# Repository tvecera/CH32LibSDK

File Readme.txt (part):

=================================================================
FORK: Additional Features in This Fork
=================================================================

- Added support for **CH32V003-GameConsole** with the name **TinyBoy**,
  using the **CH32V002J4M6** MCU (_devices/tinyboy/README.md)
- Added support for **Olimex RVPC** _devices/rvpc/README.md)
- Added shell scripts for macOS and Linux for easier programming and building

CH32LibSDK - SDK library for low-end CH32 RISC-V microcontrollers
=================================================================
Pre-alpha version 0.39, under development.

Copyright (c) 2025 Miroslav Nemecek

Panda38@seznam.cz
hardyplotter2@gmail.com
https://github.com/Panda381/CH32LibSDK
https://www.breatharian.eu/hw/ch32libsdk/index_en.html

How to compile on Windows, using command line:

- Use FAR Manager to edit source files and run BAT scripts.
- Download MounRiver Studio v1.92 http://mounriver.com/download
- Install MounRiver Studio. 
- Extract "toolchain\RISC-V Embedded GCC12" compiler to separate folder.
- Edit _c1.bat file and enter path to "bin" folder of the compiler:
   set GCC_CH32_PATH=C:\GCC_CH32\bin
- Extract "toolchain\OpenOCD\bin" tool or use openocd from _tools\openocd.
- Sometimes you may need to use WCH-LinkUtility from the ExTool\SQWTool folder.
  It may sometimes be necessary to erase the flash memory using power-off,
  because OpenOcd cannot do this.
- Compile sample using c.bat.
- Flash compiled sample using e.bat with WCH-LinkE programmer (available here,
  for example: https://pajenicko.cz/usb-programator-a-debug-adapter-wch-link ).
  For the SD card version of the console, simply upload the program to the
  SD card and load it into the processor using the boot loader.
- Clear compilation using d.bat.

AntCalc
-------
AntCalc is a wrist-worn programmable calculator with scientific functions. It
features an inexpensive CH32V002A4M6 processor, a blue-yellow 0.96" I2C OLED
display with an SSD1306 controller and a resolution of 128x64 pixels B&W
(available here, for example:
https://www.hadex.cz/m508c-displej-oled-096-128x64-znaku-iici2c-4piny-modrozluty/).
It also has 12 buttons and is powered by a CR2032 battery. The calculator works
with reverse Polish notation (RPN), which means that numbers are first entered
into the calculator's stack using the Enter button, and then the desired
operation is performed by pressing the operator. The calculator's stack has a
size of 10 registers. The lowest 4 registers are shown on the display under the
names X, Y, Z, and T. The calculator calculates in BCD code with an accuracy of
21 valid digits, along with an exponent in the range of +-99. The display shows
a maximum of 14 digits when displayed without an exponent or 11 digits with an
exponent. Functions are available for calculating direct and inverse
trigonometric functions, power function, decimal and natural logarithmic and
exponential functions. The calculator has 10 memory registers, the contents of
which are stored in flash memory even when the calculator is turned off. The
calculator can be programmed using macros containing a record of keystrokes.
Up to 10 macros, each up to 38 keys long, can be loaded into the calculator's
memory. The calculator measures 30x55 mm. A jumper is used as a switch on the
connector, which is also used to program the processor.

AntCalc calculator functions

The calculator is operated using 12 buttons. 10 buttons are digits, 1 button
is a decimal point, and 1 button is 2nd for switching between modes. In total,
you can switch between 7 states by repeatedly pressing the 2nd button. If an
error occurs during operations (division by zero or square root of a negative
number), the text "overflow" is displayed on the X register row. Pressing any
key will end the error messages and reset the X register.

0..9 ... enter a digit.

. ... Enter a decimal point. If the calculator is in exponent editing mode,
   you can use the decimal point button to return to mantissa editing.

2nd ... Switch between additional calculator functions. The selected mode is
   displayed on the top line of the display on the left.

+, -, *, :, Y^x (2nd 0..4) ... arithmetic operations between registers X and Y

y<>x (2nd 5) ... swap registers X and Y

Vx (2nd 6) ... square root

Enter (2nd 7) ... move number X to register Y

CE (2nd 8) ... Delete the last character during editing. The EE key switches to
   exponent editing, the dot key switches to mantissa editing. The CE key
   activates number editing mode if editing is not in progress.

EE (2nd 9) ... Enter exponent. Use the EE key to start editing the number shown
   on the display. Use the decimal point key to switch to mantissa editing.

+/- (2nd .) ... Change the sign of the mantissa or exponent of the number on
   the display.

sin (2x2nd 0) ... sine

asin (2x2nd 1) ... arc sine

log (2x2nd 2) ... decimal logarithm

ln (2x2nd 3) ... natural logarithm

cos (2x2nd 4) ... cosine

acos (2x2nd 5) ... arccosine

exp10 (2x2nd 6) ... decimal exponent

exp (2x2nd 7) ... natural exponent

tan (2x2nd 8) ... tangent

atan (2x2nd 9) ... arctangent

1/x (2x2nd .) ... reciprocal value

RCL0..RCL9 (3x2nd 0..9) ... recall memory contents 0 to 9

PI (3x2nd .) ... Pi number

STO0..STO9 (4x2nd 0..9) ... Saving a number to memory 0 to 9. The content is
   stored in flash memory even when the device is turned off.

DEG (4x2nd .) ... Switching the angular measure of goniometric functions
   between degrees (DEG) and radians (RAD). The selected setting is displayed
   in the middle of the top line of the display and is stored in flash memory.

RUN0..RUN9 (5x2nd 0..9) ... Play macro number 0 to 9.

INT (5x2nd .) ... Cut off the decimal part of the number (rounding to whole
   numbers towards zero).

PRG0..PRG9 (6x2nd 0..9) ... Start recording a macro into program number 0 to 9.
   The codes of the pressed keys are stored in memory. Up to 38 button codes
   can be stored in one macro. Presses of the 2nd button are not stored in the
   program - the resulting function code is stored as 1 code. During macro
   recording, the text PROG0..PROG9 flashes in the upper right corner of the
   display, indicating that recording is in progress. If the number of buttons
   is exceeded, the indicator remains lit but stops flashing to indicate that
   buttons are no longer being stored. Macro recording can be stopped by
   pressing any of the PRG0 to PRG9 functions (it is not necessary to use the
   same macro number).

C (6x2nd .) ... Clears the calculator's registers. The contents of the memory
   and programs are retained. Turning the calculator off and on has the same
   effect.

Notes on construction:

The calculator uses a very inexpensive Chinese processor CH32V002A4M6. It is
housed in an SOP16 package with large pin spacing, making the calculator's
design suitable even for novice designers. The calculator has two eyelets on
the bottom for attaching a strap. To simplify the design, a jumper plugged into
the connector, which is also used to program the calculator's processor, was
used as a switch. When switched on, the jumper is plugged into the two pins on
the right, and when switched off, it is plugged into the two pins on the left.
A two-color, blue-yellow OLED display with an SSD1306 controller and a
resolution of 128x64 was used. The display is actually monochrome, with the top
16 lines displayed in yellow and the next 48 lines in blue. Alternatively, a
monochrome display can also be used. I leave the design of the top cover with
button labels to other designers  in the prototype, I only used a paper label
with cut-out holes for the buttons.

>>> Source codes and all necessary documentation of the AntCalc calculator can
be found in the CH32LibSDK library in the ch32\DEVICE\ folder.
https://github.com/Panda381/CH32LibSDK/tree/main/ch32/DEVICE <<<

BeatleBoyPad (BeatleBoy, BeatlePad)
-----------------------------------
BeatleBoyPad is dual console with interchangeable ROM cartridges. It consists
of two consoles. The first console, BeatleBoy, contains 128x64 pixel black and
white OLED I2C display with SSD1306 controller, built-in speaker and 6 buttons
(4 directional arrows and A and B buttons). The console is powered by CR2032
battery. The second console, BeatlePad, has black and white output to VGA
monitor and connector for external speaker. Cartridge with program contains
cheap Chinese processor CH32V002J4M6, CH32V003J4M6 or CH32V006F8P6. Note: for
processor V006 different cartridge wiring than for processors V002 and V003 is
used.

The cartridges are common to both consoles. The processor in the cartridge
distinguishes between the two consoles based on the voltage and switches to
the appropriate mode accordingly. Due to the console's auto-detection, it is
therefore necessary to maintain the power supply used - the BeatleBoy console
is powered by a 3V battery, while the BeatlePad console is powered by a 5V
external source. In addition to detecting the supply voltage, the processor
in the BeatlePad console also detects the connection of a VGA cable. The
program in the console will only start after connecting a VGA monitor. This
is so that the cartridge can be reprogrammed in the programmer, as the VGA
console also uses programming pin.

There are 25 games available for the console. All prepared games can be
programmed into all types of cartridges - with V002, V003, or V006 processors.
The V002 processor variant has more RAM available than the V003 processor, and
the output to the VGA monitor is via SPI controller, which allows the use of
higher video mode resolutions (this is not used in the prepared games). The
V006 processor has more RAM than the V002 processor. However, unless required
by the software, it is recommended to use the CH32V003J4M6 processor. Although
this is an older type of processor, its advantage is higher oscillator
stability and therefore less noise in the VGA image.

When constructing the device, it is necessary to use resistors with 1%
accuracy, otherwise button presses may be detected incorrectly. The
brightness of the OLED display is kept low to minimize battery consumption.
The current voltage of the CR2032 battery is displayed when most programs
start. The measurement is performed using the internal reference of the
processor, and therefore the displayed value may vary by up to 10% and
should therefore be taken as a guide only. Pay attention to the pin layout
of the display - there are usually two versions, with the pin order
VCC-GND-SCL-SDA or GND-VDD-SCL-SDA. Both variants are available on the
printed circuit board (alternatively, the display can be connected
interchangeably via a pin header). The OLED display is used here in an
inverted position compared to other consoles - the image rotation is defined
in the display initialization sequence.

An internal HSI RC oscillator is used for VGA image output. Its frequency is
not stabilized by a crystal, so slight signal timing deviations and image
noise must be expected. The V003 processor has slightly lower image noise than
the V002 and V006 processors. Some VGA monitors may not display the image due
to the low quality of the image signal timing.

Programs can be loaded into the cartridge using the WCH-LinkE programmer
(available, for example, here:
https://pajenicko.cz/usb-programator-a-debug-adapter-wch-link). Pin number 4
on the cartridge is left as an option for reprogramming processors requiring
2-wire programming (SWDIO+SWCLK, e.g., CH32X035). Currently, this option is
not used, and it is possible to use this pin as a blind pin to facilitate
cartridge insertion orientation (i.e., cut off pin number 4 on the cartridge
and plug the corresponding pin on the console, e.g., with heat shrink tubing).

BeatleCalc with emulation of Sinclair Scientific and Datamath calculators
-------------------------------------------------------------------------
BeatleCalc is a minimalist scientific calculator, supplemented with emulators
of calculators Sinclair Scientific (1974, TMC0805 processor) and Texas
Instruments TI-2500 Datamath (1972, TMS0803 processor). The calculator uses BCD
code internally, so it does not suffer from the inaccuracies of binary
representation of decimal numbers. It calculates internally with an accuracy
of 13 digits. The exponent ranges from -99 to +99. It includes calculations
of direct and inverse trigonometric functions, in radians and degrees, natural
and decimal logarithmic and exponential functions, powers and roots. It prefers
operation priority, and parentheses can also be used. Numbers can be stored in
4 memory registers, which retain their value even when the power is turned off.

Switching the calculator mode between emulation or BeatleCalc calculator:

- Press and hold the number 1 to 3: 1 selects the default BeatleCalc
  calculator, 2 selects Sinclair Scientific emulation, 3 selects Datamath
  emulation.
- Press the C button briefly. This will reset the calculator.
- Release the number 1 to 3 key. While you hold the key, the selected mode text
  will appear on the display: "CALCUL" is the default BeatleCalc calculator,
  "SINCLAIr" is Sinclair Scientific emulation, and "DATAMATH" is Datamath
  emulation.

Controls for emulated calculators can be found in the relevant calculator
manuals. Please note that the Sinclair calculator uses RPN reverse logic
- you must first enter the number and then the desired operation (typically '+'
is used to insert a number into the stack). Emulators use only some of the
calculator buttons - the layout of the buttons used can be seen in the pictures
of the calculator labels.

BeatleCalc calculator functions:

STO1..STO4 ... Stores the number on the display in memory registers 1 to 4.
   The number is stored in the flash memory of the second CPU2 processor and
   remains available even after the power is turned off.

RCL1..RCL4 ... Displaying a number from memory registers 1 to 4.

CE ... Clearing the last digit or turning off the error indicator. If an
   unedited number is displayed, the calculator switches to edit mode.

2nd, 3rd ... Selection of alternative functions. An indicator appears at the
   first position on the display (2nd=upper line, 3rd=lower line).

= ... Calculation of the expression. Repeated pressing repeats the last
   operation with the last operand.

EE ... Exponent input mode. If an unedited number is displayed, the calculator
   enters exponent edit mode. Press the decimal point key to enter mantissa
   edit mode.

LOG, EXP10 ... Logarithmic and exponential functions with a decimal base.

LN, EXP ... Logarithmic and exponential functions with a natural base.

TAN, ATAN, SIN, ASIN, COS, ACOS ... Trigonometric functions calculated in
   radians.

TAND, ATAND, SIND, ASIND, COSD, ACOSD ... Trigonometric functions calculated
   in degrees.

Notes on construction:

Two CH32V002A4M6 processors were used in the calculator. The reason for this
choice (apart from the low price) is that they are easy to solder, which is
also suitable for beginners. The CPU1 processor is the main processing unit.
The CPU2 processor controls the display multiplexer and is used to store the
configuration and memory registers. The photos show a prototype of the
calculator  I focused primarily on the calculator software, not the design,
so I recommend choosing your own calculator design. A printed circuit board can
be used as the top cover of the calculator. For the prototype, I printed the
label on paper, covered it with transparent adhesive tape on both sides, and
cut out the holes for the buttons with a skin punch. I recommend covering the
display with red Plexiglas, otherwise it may be difficult to read in bright
light. The capacitors should be soldered horizontally so that they do not
interfere with the top cover. I used a 1-digit LED display as the digit in the
first position. You do not have to use it, because only the sign of the number
and the indicators for the 2nd and 3rd buttons (segments A, D, and G) are
displayed in this position. You can replace the digit display with a flat red
LED connected between signals D1 and SG. The 2nd and 3rd indicators are not
necessary. I did not solve the power supply issue in the prototype. It is also
possible to use, for example, a 3.7V battery with a charging circuit. A CR2032
battery may not be powerful enough, as the display may have a high power
consumption.

The calculator firmware consists of two parts. In the ch32\DEVICE\BeatleCalc
folder, you will find the main executive firmware, which you will upload to the
CPU1 processor (e.g., using the WCH-LinkE programmer:
https://pajenicko.cz/usb-programator-a-debug-adapter-wch-link).
The ch32\DEVICE\BeatleCalc_CPU2 folder contains the firmware for the second
processor, CPU2. Until the firmware is loaded into both processors and
communication between them is working, the display will remain dark. If you
need to find a malfunction, use the ch32\DEMO\LED program, in which you will
enter the appropriate pins and use the control LED to check whether the signals
are OK.

Note: Calculator emulation was verified using the emulator
https://static.righto.com/calculator/sinclair_scientific_simulator.html by
Ken Shirriff. No physical calculators were available to verify functionality,
so it is possible that the calculators' functions may not correspond exactly
to the original.

>>> Source codes and all necessary documentation can be found in the CH32LibSDK
  library in the ch32\DEVICE\ folder. <<<

BabyBoy
-------
BabyBoy is the simplest game mini-console with 6 buttons, an inexpensive
CH32V002A4M6 processor (price 10 cents), a built-in speaker, and 128x64 pixel
black-and-white OLED I2C display with an SSD1306 controller. The console is
powered by a CR2032 battery, or it can be powered by an external 3.3V source
via the programming connector. Thanks to simplifications and the easy soldering
of the processor in the SOP16 package with a pin pitch of 1.27mm, the console
is primarily intended for beginners as a kit for their first introduction to
electronics.

Pay attention to the pin layout on the display ï¿½ there are usually two
versions, with the pin order VCC-GND-SCL-SDA or GND-VDD-SCL-SDA. I used two pin
headers on the circuit board for both display versions so that I could change
the displays and insert them into the correct position.

BabyBoy does not include an SD card. Programs must be uploaded to the processor
using the WCH-LinkE programmer (available here, for example:
https://pajenicko.cz/usb-programator-a-debug-adapter-wch-link).

BabyPad
-------
BabyPad is a mini game console with 7 buttons, CH32V002A4M6 processor,
25 MHz crystal (optional), audio output, and VGA mono B&W output to a
monitor. The crystal and associated capacitors are not required - if
the software detects that the crystal is not available, it will use the
internal HSI oscillator, tuned to a frequency close to 25 MHz. In this
case, the image will be slightly noisy, but still usable - it depends
on the monitor used how well it handles image stabilization. BabyPad
uses a processor in an SOP16 package with a pin pitch of 1.27 mm, which
makes soldering easy even for beginners. Together with its simple design
(and the option of not installing a crystal), it is primarily intended
for beginners as a kit for their first introduction to electronics.

BabyPad does not include an SD card. Programs must be uploaded to the
processor using the WCH-LinkE programmer (available here, for example:
https://pajenicko.cz/usb-programator-a-debug-adapter-wch-link).

In the _devices\babypad\diagram\ folder, you will find diagram of the
BabyPad console. In the !Babypad folder, you will find a ready-made
sample programs for the BabyPad. The Babypad folder contains source
codes of sample applications for BabyPad.

BabyPC - WCH80
--------------
The BabyPC - WCH80 is an inexpensive mini-computer with two CH32V002
processors, created based on the ZX80 computer. It is not an emulator;
the computer does not emulate the ZX80 computer's ROM, nor does it emulate Z80
machine instructions. It was created as a completely independent computer with
the BASIC80 programming language and VGA monitor output, only replicating the
ZX80's functionality as closely as possible. It uses a CH32V002A4M6 processor,
which, thanks to its large 1.27 mm pin pitch, is suitable for easy soldering
even for novice designers. Together with other THT components, the WCH80 is
particularly suitable as a kit for novice designers. The built-in BASIC80
programming language is used to familiarize users with computer programming and
to try out how programmers programmed in the 1980s.

The computer does not contain a storage medium for saving programs. Your own
programs can be saved directly to the processor's flash memory. There are 14
memory slots available, i.e. 14 places to store your own programs, numbered 0
to 13. Slot 0 is located in the main CPU1 processor. When stored in slot 0,
data variables are also stored along with the program (more precisely, only the
first half of the memory with variables). Slot 0 is automatically loaded into
the program memory when the computer is turned on. Memory slots 1 to 13 are
located in the second processor, CPU2. All slots allow the entire memory with
the program to be stored, except for the last slot 13, which is only half the
size.

After initial programming, the processors contain 28 sample programs and games
written in BASIC80. Once the processors have been programmed, the programmer is
no longer needed, but it can be useful if you want to back up the contents of
the processors to a PC or if you want to change program versions. Using slot 0,
programs can also be transferred between the processors' memory backups by
copying between the CPU1 and CPU2 processors.

In addition to the BASIC80 firmware, games and programs written in C can also
be uploaded to the computer using a programmer. There are 25 sample games
available. The games can be found in the CH32LibSDK library. However, it is
important to remember that reprogramming the CPU1 processor will also overwrite
the contents of slot 0. The contents of slots 1 to 13 in CPU2 will not change
when games are loaded. For games in C code, the following keys are usually used
for control: 8, F=right, 7, E=up, 5, S=left, 6, D=down, A, space=action, B,
NEW LINE=alternative action, X, P=info, Y, 0=back.

More details and supporting documents can be found on a separate page:
https://www.breatharian.eu/hw/wch80/index_en.html or on GitHub:
https://github.com/Panda381/WCH80.

Pidiboy
-------
PidiBoy is a mini game console with 7 buttons, an inexpensive CH32V006F8P6
processor (costing 20 cents), a microSD card, a built-in speaker, audio
output, and a 128x64 pixel black-and-white OLED I2C display with an SSD1306
controller. https://pajenicko.cz/graficky-oled-displej-096-128x64-i2c-bily
The console is equipped with an ME2108A33PG step-up voltage converter
with a 3.3V output and can therefore be operated from 1 or 2 AA or AAA
batteries in the voltage range of 1.1V to 3.3V, or the console can be
powered by an external 3.3V source via the programming connector. Programs
can be run from an SD card using a boot loader, which loads the program into
the processor's flash memory. Boot loader controls: up/down arrows - move the
cursor by 1 item, left/right arrows - move the cursor by 1 page, A - start
program or change folder, B - display voltage or move to parent folder, Y -
run program located in flash memory. Pay attention to the pin layout on the
display ï¿½ there are usually two versions, with the pin order VCC-GND-SCL-SDA
or GND-VDD-SCL-SDA. I used two pin headers on the circuit board for both
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
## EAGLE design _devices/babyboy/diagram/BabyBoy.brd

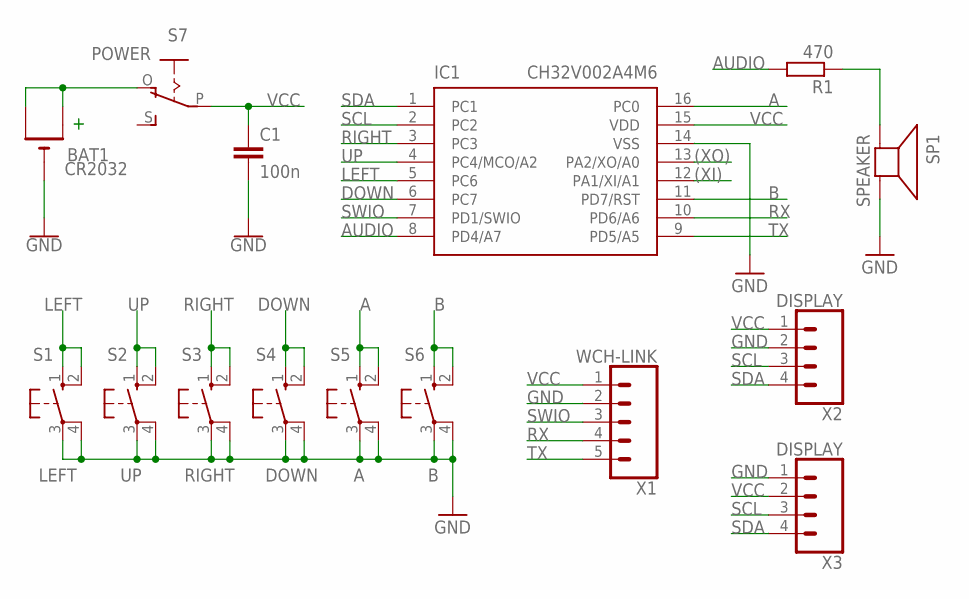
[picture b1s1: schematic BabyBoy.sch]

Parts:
BAT1: CR2032; CR2032-THRU
C1: 100n; C050-024X044
IC1: CH32V002A4M6; SOP16
R1: 470; 0204/7
S1: LEFT; B3F-10XX
S2: UP; B3F-10XX
S3: RIGHT; B3F-10XX
S4: DOWN; B3F-10XX
S5: A; B3F-10XX
S6: B; B3F-10XX
S7: POWER; EG1218
SP1: SPEAKER; AL60P
X1: WCH-LINK; 1X05_LONGPADS
X2, X3: DISPLAY; 1X04

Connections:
(XI): IC1.12 (PA1/XI/A1)
(XO): IC1.13 (PA2/XO/A0)
A: IC1.16 (PC0), S5.1 (S), S5.2 (S1)
AUDIO: IC1.8 (PD4/A7), R1.2
B: IC1.11 (PD7/RST), S6.1 (S), S6.2 (S1)
DOWN: IC1.6 (PC7), S4.1 (S), S4.2 (S1)
GND: BAT1.-, C1.2, IC1.14 (VSS), S1.3, S1.4 (P1), S2.3, S2.4 (P1), S3.3, S3.4 (P1), S4.3, S4.4 (P1), S5.3, S5.4 (P1), S6.3, S6.4 (P1), SP1.2 (-), X1.2, X2.2, X3.1
LEFT: IC1.5 (PC6), S1.1 (S), S1.2 (S1)
unnamed: R1.1, SP1.1 (+)
RIGHT: IC1.3 (PC3), S3.1 (S), S3.2 (S1)
RX: IC1.10 (PD6/A6), X1.4
SCL: IC1.2 (PC2), X2.3, X3.3
SDA: IC1.1 (PC1), X2.4, X3.4
SWIO: IC1.7 (PD1/SWIO), X1.3
TX: IC1.9 (PD5/A5), X1.5
UP: IC1.4 (PC4/MCO/A2), S2.1 (S), S2.2 (S1)
VBAT: BAT1.+1 (+), BAT1.+2 (+1), S7.O
VCC: C1.1, IC1.15 (VDD), S7.P, X1.1, X2.1, X3.2

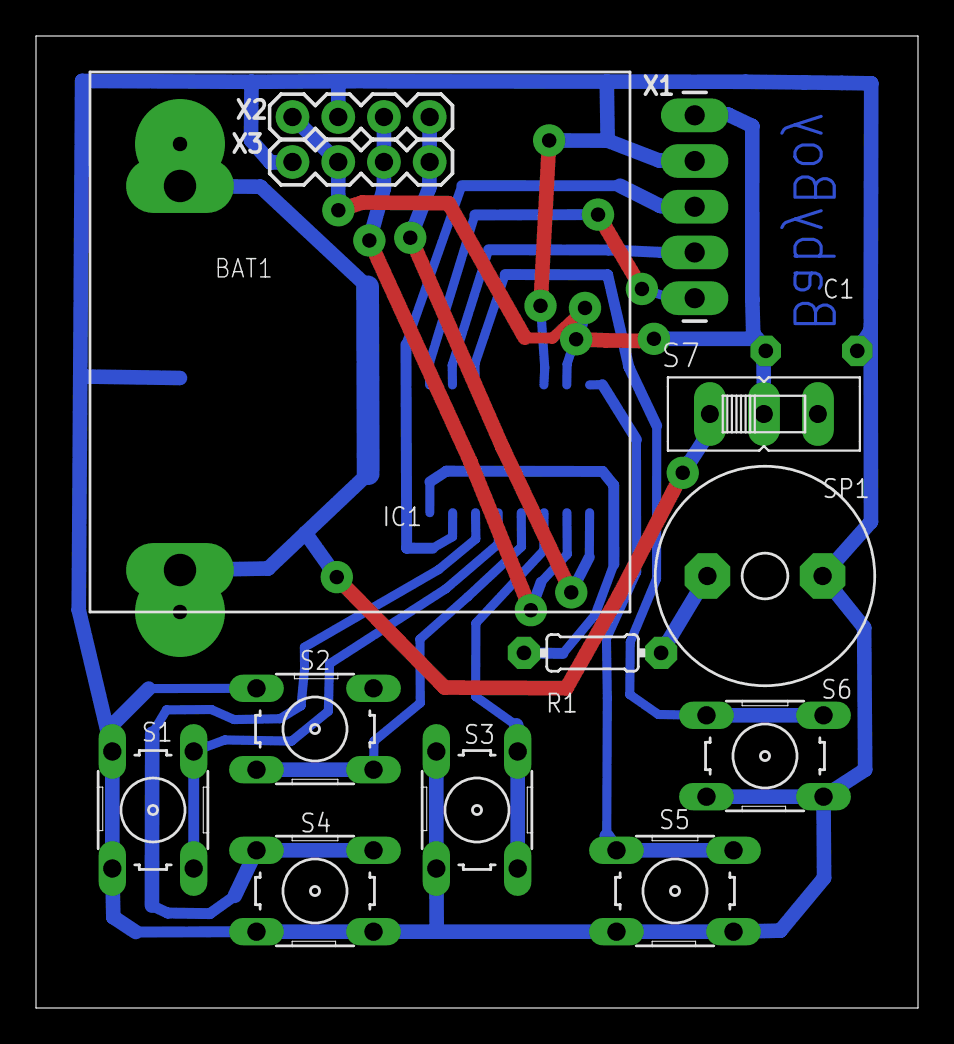
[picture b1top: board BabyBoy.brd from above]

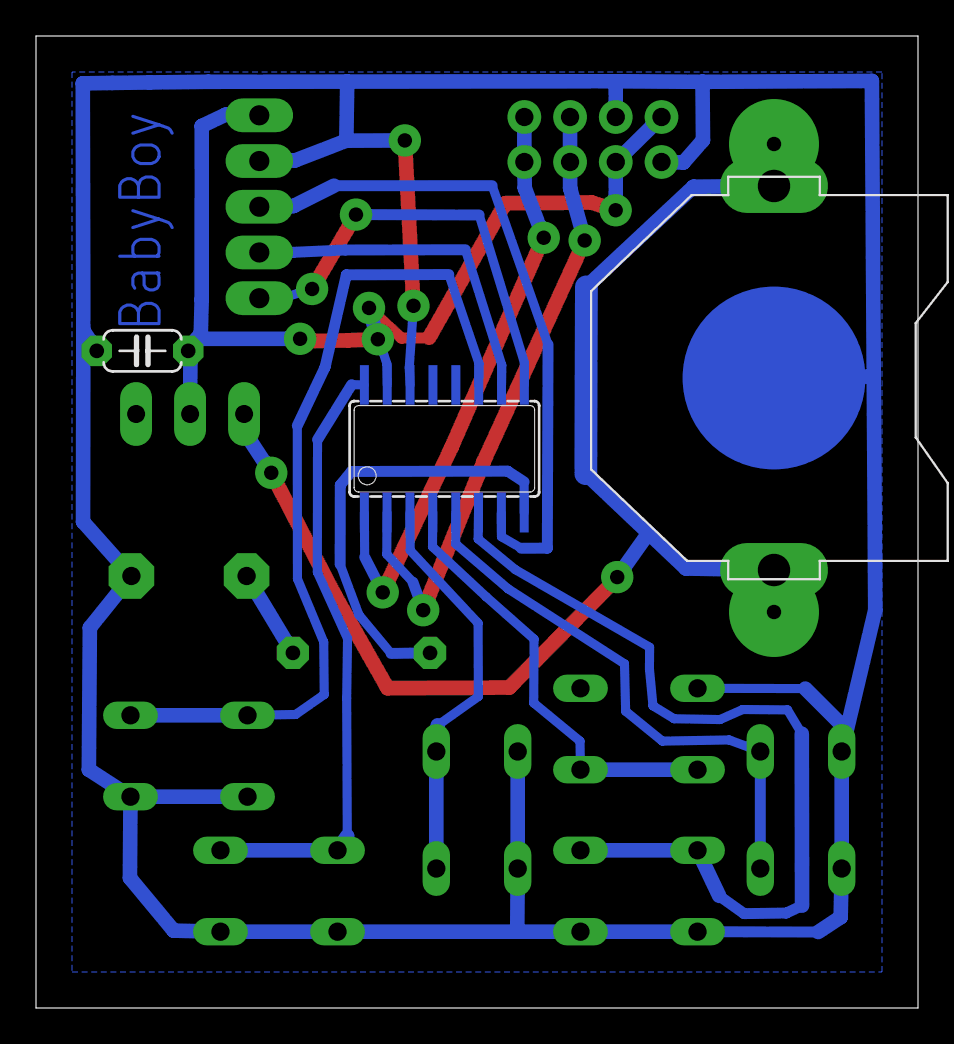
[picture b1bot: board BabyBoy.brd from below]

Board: 2 copper layers, 49.0 x 54.0 mm, 15 parts (3 on the bottom side), 16 nets.

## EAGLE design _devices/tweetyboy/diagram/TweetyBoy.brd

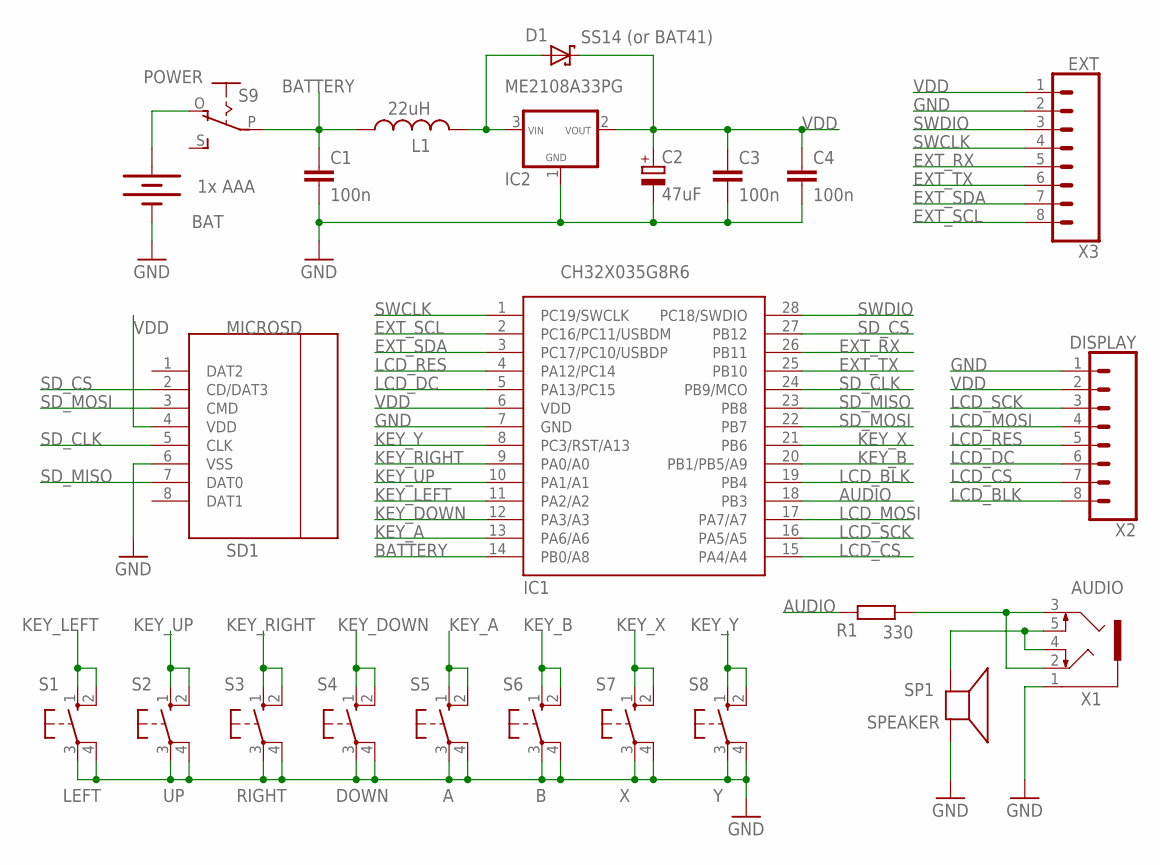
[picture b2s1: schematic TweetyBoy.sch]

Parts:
BAT: 1x AAA; BATTERY-AAA-KIT
C1, C3, C4: 100n; C050-024X044
C2: 47uF; E2-5
D1: SS14 (or BAT41); DO35-7
IC1: CH32X035G8R6; QSOP28
IC2: ME2108A33PG; SOT89-R
L1: 22uH; POWER-CHOKE_WE-TPC
R1: 330; 0204/7
S1: LEFT; B3F-10XX
S2: UP; B3F-10XX
S3: RIGHT; B3F-10XX
S4: DOWN; B3F-10XX
S5: A; B3F-10XX
S6: B; B3F-10XX
S7: X; B3F-10XX
S8: Y; B3F-10XX
S9: POWER; EG1218
SD1: MICROSD
SP1: SPEAKER; AL60P
X1: AUDIO; 1503_09
X2: DISPLAY; 1X08_LONGPADS
X3: EXT; 1X08_LONGPADS

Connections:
AUDIO: IC1.18 (PB3), R1.2
BATTERY: C1.1, IC1.14 (PB0/A8), L1.1, S9.P
EXT_RX: IC1.26 (PB11), X3.5
EXT_SCL: IC1.2 (PC16/PC11/USBDM), X3.8
EXT_SDA: IC1.3 (PC17/PC10/USBDP), X3.7
EXT_TX: IC1.25 (PB10), X3.6
GND: BAT.GND@1 (-), C1.2, C2.-, C3.2, C4.2, IC1.7 (GND), IC2.1 (GND), S1.3, S1.4 (P1), S2.3, S2.4 (P1), S3.3, S3.4 (P1), S4.3, S4.4 (P1), S5.3, S5.4 (P1), S6.3, S6.4 (P1), S7.3, S7.4 (P1), S8.3, S8.4 (P1), SD1.6 (VSS), SP1.2 (-), X1.1, X2.1, X3.2
KEY_A: IC1.13 (PA6/A6), S5.1 (S), S5.2 (S1)
KEY_B: IC1.20 (PB1/PB5/A9), S6.1 (S), S6.2 (S1)
KEY_DOWN: IC1.12 (PA3/A3), S4.1 (S), S4.2 (S1)
KEY_LEFT: IC1.11 (PA2/A2), S1.1 (S), S1.2 (S1)
KEY_RIGHT: IC1.9 (PA0/A0), S3.1 (S), S3.2 (S1)
KEY_UP: IC1.10 (PA1/A1), S2.1 (S), S2.2 (S1)
KEY_X: IC1.21 (PB6), S7.1 (S), S7.2 (S1)
KEY_Y: IC1.8 (PC3/RST/A13), S8.1 (S), S8.2 (S1)
LCD_BLK: IC1.19 (PB4), X2.8
LCD_CS: IC1.15 (PA4/A4), X2.7
LCD_DC: IC1.5 (PA13/PC15), X2.6
LCD_MOSI: IC1.17 (PA7/A7), X2.4
LCD_RES: IC1.4 (PA12/PC14), X2.5
LCD_SCK: IC1.16 (PA5/A5), X2.3
unnamed: SP1.1 (+), X1.4, X1.5
unnamed: BAT.PWR@1 (+), S9.O
unnamed: D1.A, IC2.3 (IN), L1.2
unnamed: R1.1, X1.2, X1.3
SD_CLK: IC1.24 (PB9/MCO), SD1.5 (CLK)
SD_CS: IC1.27 (PB12), SD1.2 (CD/DAT3)
SD_MISO: IC1.23 (PB8), SD1.7 (DAT0)
SD_MOSI: IC1.22 (PB7), SD1.3 (CMD)
SWCLK: IC1.1 (PC19/SWCLK), X3.4
SWDIO: IC1.28 (PC18/SWDIO), X3.3
VDD: C2.+, C3.1, C4.1, D1.C, IC1.6 (VDD), IC2.2 (VOUT), SD1.4 (VDD), X2.2, X3.1

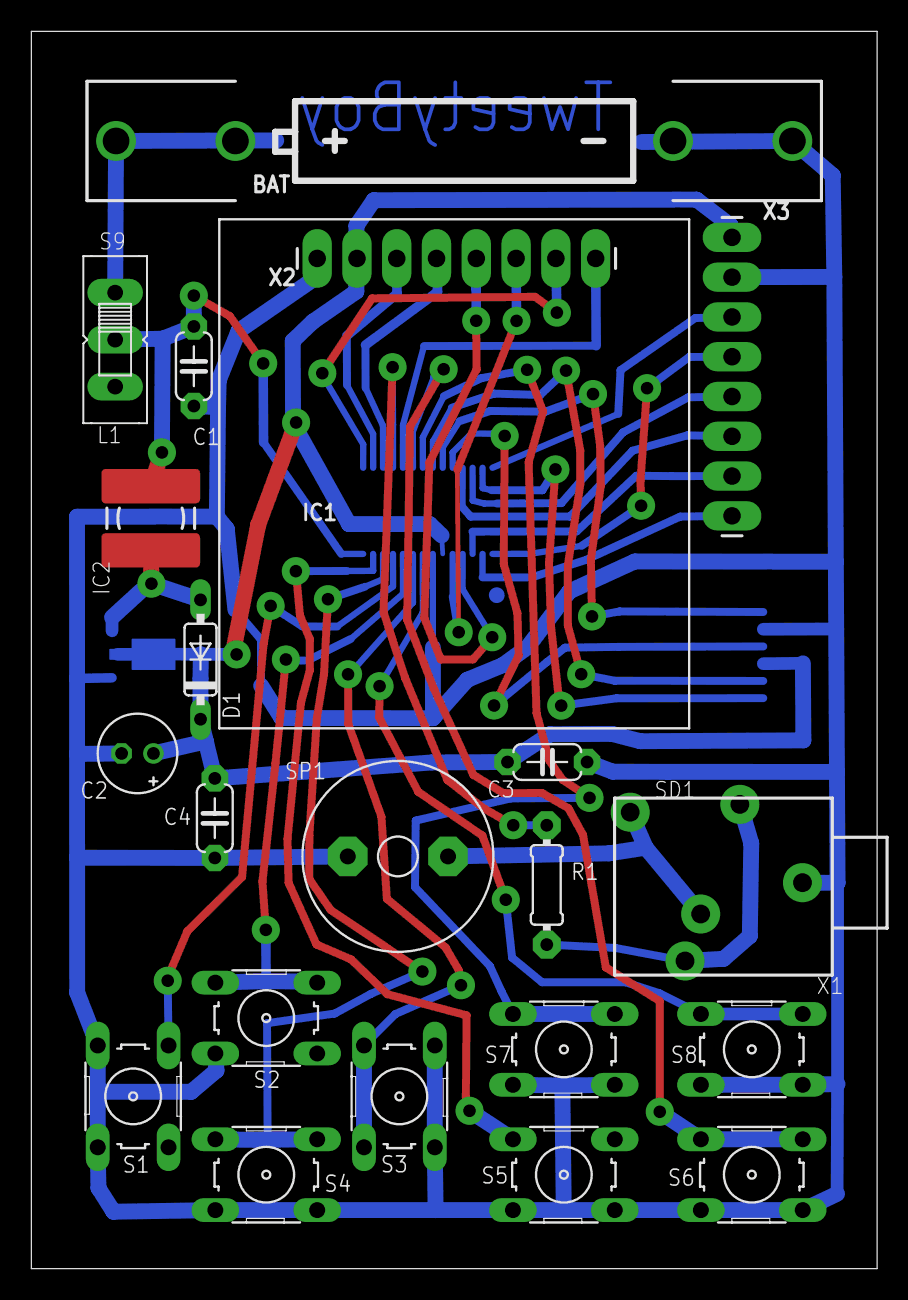
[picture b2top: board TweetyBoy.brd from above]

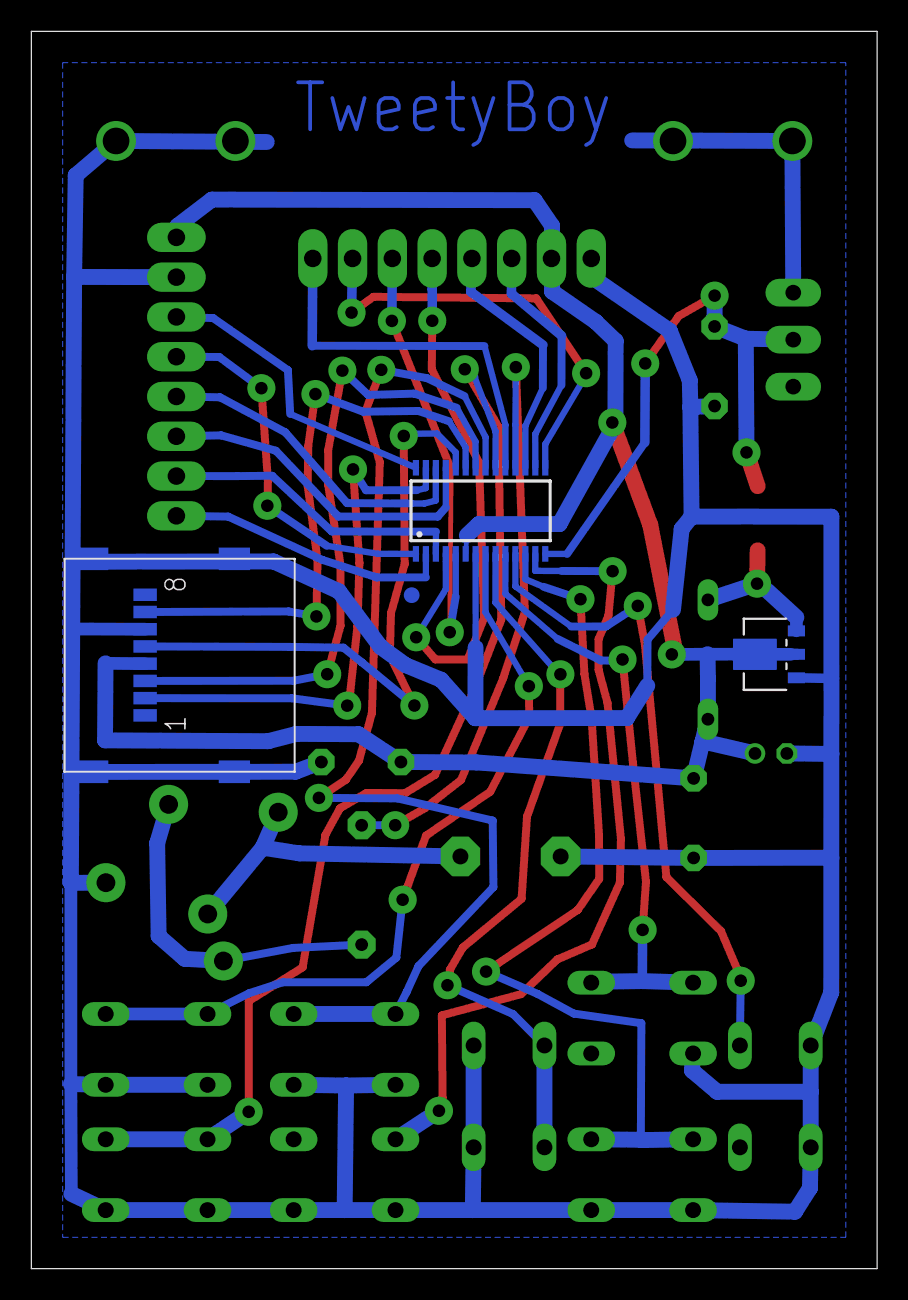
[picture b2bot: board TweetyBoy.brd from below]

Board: 2 copper layers, 54.0 x 79.0 mm, 24 parts (3 on the bottom side), 32 nets.

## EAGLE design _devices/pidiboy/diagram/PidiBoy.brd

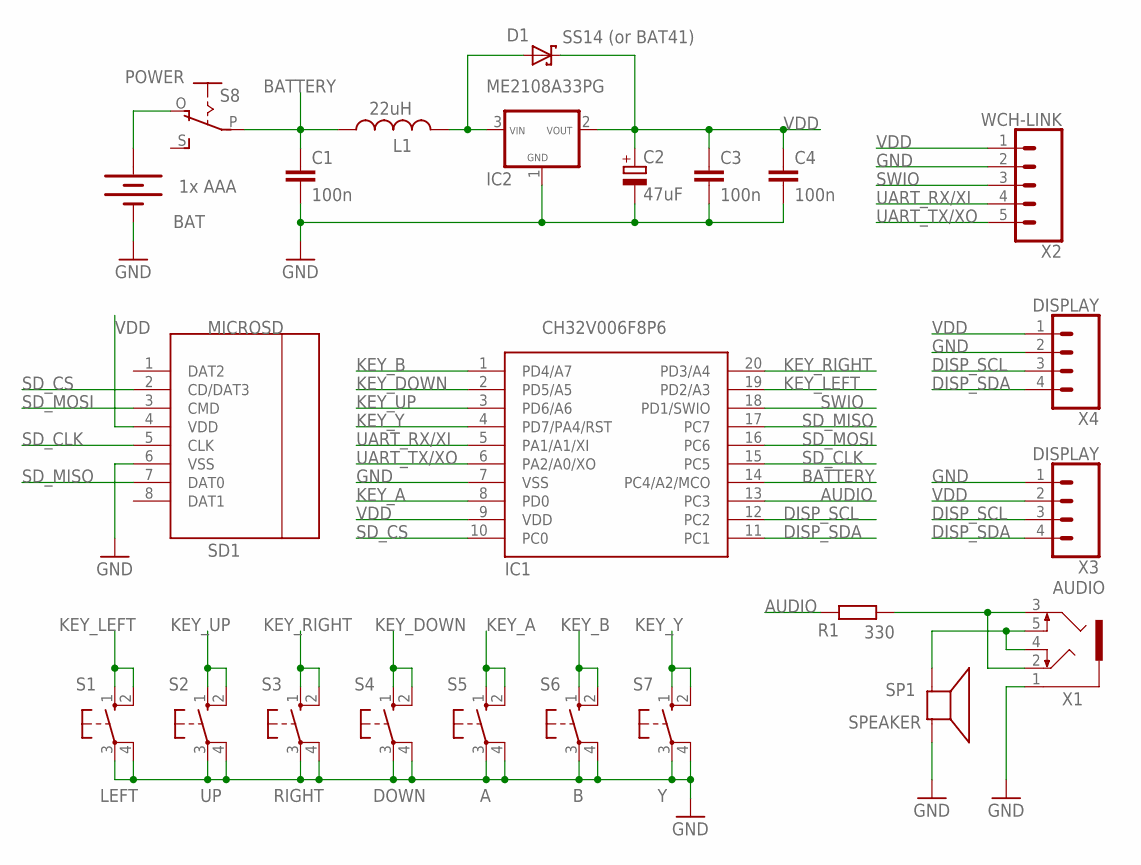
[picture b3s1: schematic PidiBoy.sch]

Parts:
BAT: 1x AAA; BATTERY-AAA-KIT
C1, C3, C4: 100n; C050-024X044
C2: 47uF; E2-5
D1: SS14 (or BAT41); DO35-7
IC1: CH32V006F8P6; TSSOP20
IC2: ME2108A33PG; SOT89-R
L1: 22uH; POWER-CHOKE_WE-TPC
R1: 330; 0204/7
S1: LEFT; B3F-10XX
S2: UP; B3F-10XX
S3: RIGHT; B3F-10XX
S4: DOWN; B3F-10XX
S5: A; B3F-10XX
S6: B; B3F-10XX
S7: Y; B3F-10XX
S8: POWER; EG1218
SD1: MICROSD
SP1: SPEAKER; AL60P
X1: AUDIO; 1503_09
X2: WCH-LINK; 1X05_LONGPADS
X3, X4: DISPLAY; 1X04

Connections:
AUDIO: IC1.13 (PC3), R1.2
BATTERY: C1.1, IC1.14 (PC4/A2/MCO), L1.1, S8.P
DISP_SCL: IC1.12 (PC2), X3.3, X4.3
DISP_SDA: IC1.11 (PC1), X3.4, X4.4
GND: BAT.GND@1 (-), C1.2, C2.-, C3.2, C4.2, IC1.7 (VSS), IC2.1 (GND), S1.3, S1.4 (P1), S2.3, S2.4 (P1), S3.3, S3.4 (P1), S4.3, S4.4 (P1), S5.3, S5.4 (P1), S6.3, S6.4 (P1), S7.3, S7.4 (P1), SD1.6 (VSS), SP1.2 (-), X1.1, X2.2, X3.1, X4.2
KEY_A: IC1.8 (PD0), S5.1 (S), S5.2 (S1)
KEY_B: IC1.1 (PD4/A7), S6.1 (S), S6.2 (S1)
KEY_DOWN: IC1.2 (PD5/A5), S4.1 (S), S4.2 (S1)
KEY_LEFT: IC1.19 (PD2/A3), S1.1 (S), S1.2 (S1)
KEY_RIGHT: IC1.20 (PD3/A4), S3.1 (S), S3.2 (S1)
KEY_UP: IC1.3 (PD6/A6), S2.1 (S), S2.2 (S1)
KEY_Y: IC1.4 (PD7/PA4/RST), S7.1 (S), S7.2 (S1)
unnamed: SP1.1 (+), X1.4, X1.5
unnamed: BAT.PWR@1 (+), S8.O
unnamed: D1.A, IC2.3 (IN), L1.2
unnamed: R1.1, X1.2, X1.3
SD_CLK: IC1.15 (PC5), SD1.5 (CLK)
SD_CS: IC1.10 (PC0), SD1.2 (CD/DAT3)
SD_MISO: IC1.17 (PC7), SD1.7 (DAT0)
SD_MOSI: IC1.16 (PC6), SD1.3 (CMD)
SWIO: IC1.18 (PD1/SWIO), X2.3
UART_RX/XI: IC1.5 (PA1/A1/XI), X2.4
UART_TX/XO: IC1.6 (PA2/A0/XO), X2.5
VDD: C2.+, C3.1, C4.1, D1.C, IC1.9 (VDD), IC2.2 (VOUT), SD1.4 (VDD), X2.1, X3.2, X4.1

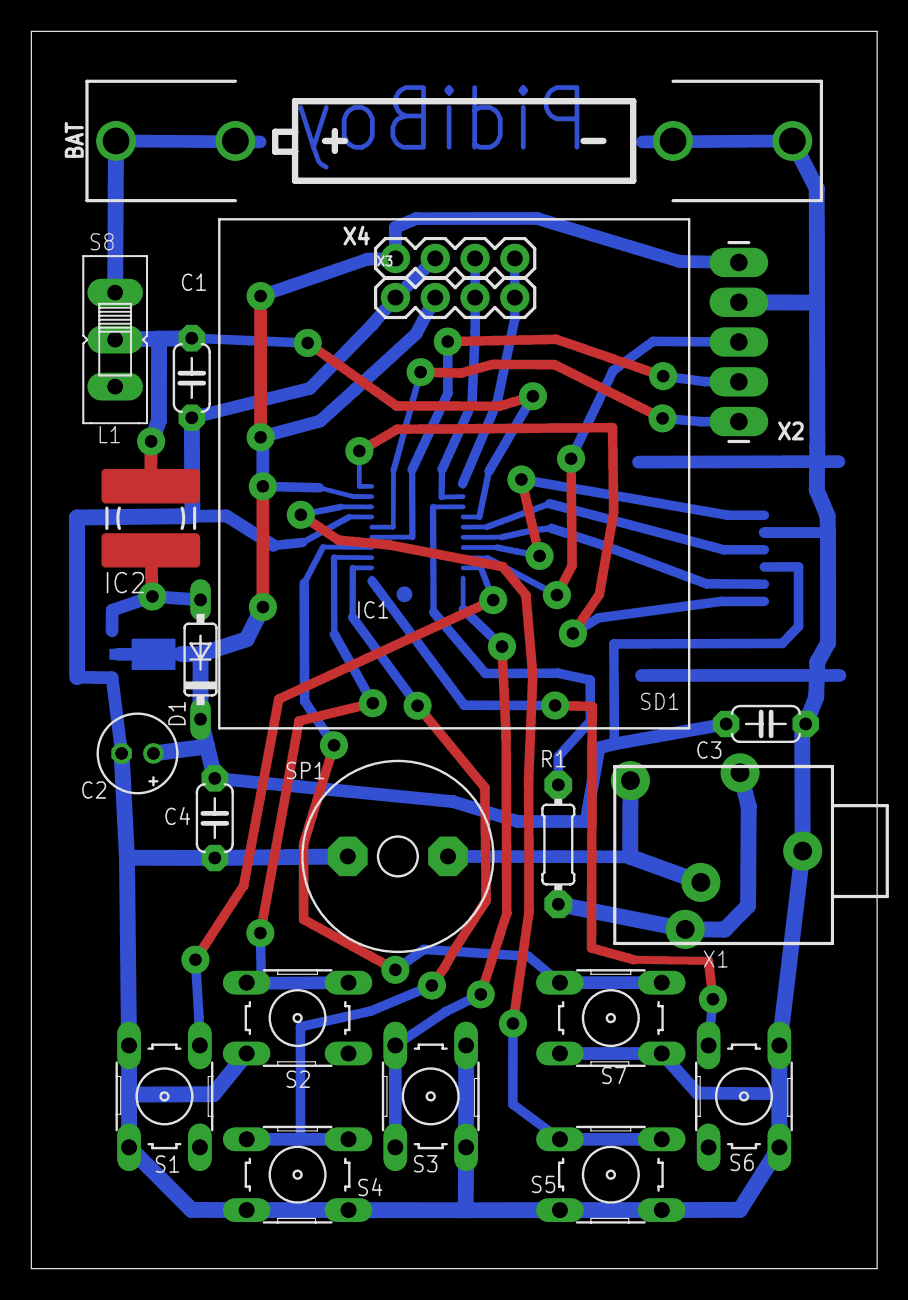
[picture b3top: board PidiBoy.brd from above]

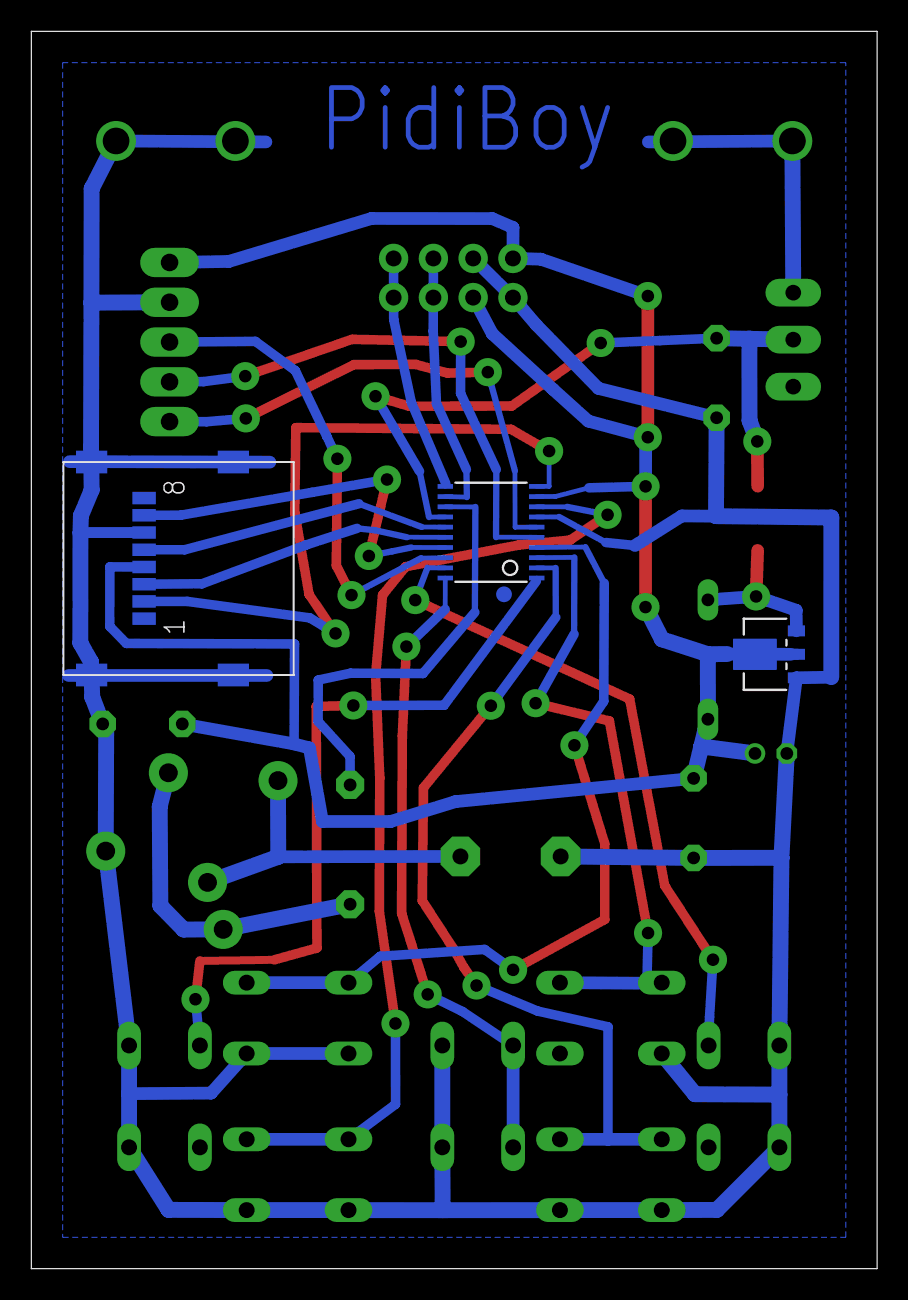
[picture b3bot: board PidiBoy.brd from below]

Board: 2 copper layers, 54.0 x 79.0 mm, 24 parts (3 on the bottom side), 24 nets.

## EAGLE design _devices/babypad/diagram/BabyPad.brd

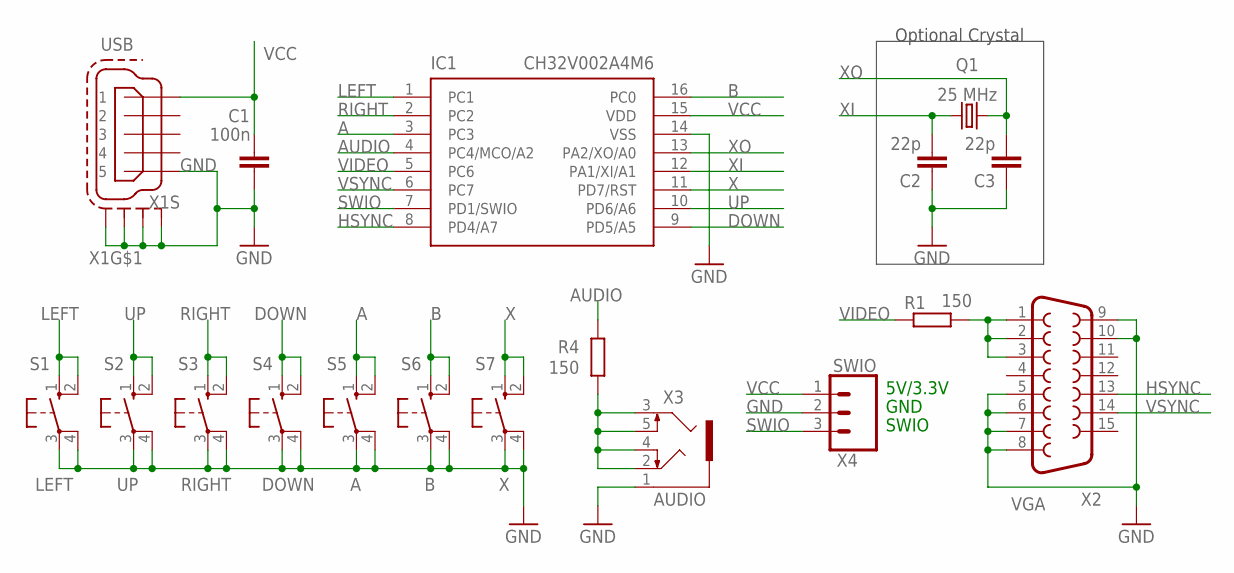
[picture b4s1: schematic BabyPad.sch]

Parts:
C1: 100n; C050-024X044
C2, C3: 22p; C050-024X044
IC1: CH32V002A4M6; SOP16
Q1: 25 MHz; HC49U-V
R1, R4: 150; 0204/7
S1: LEFT; B3F-10XX
S2: UP; B3F-10XX
S3: RIGHT; B3F-10XX
S4: DOWN; B3F-10XX
S5: A; B3F-10XX
S6: B; B3F-10XX
S7: X; B3F-10XX
X1: USB; 32005-201
X2: VGA; HDF15H
X3: AUDIO; 1503_09
X4: SWIO; 1X03_LONGPADS

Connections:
A: IC1.3 (PC3), S5.1 (S), S5.2 (S1)
AUDIO: IC1.4 (PC4/MCO/A2), R4.2
B: IC1.16 (PC0), S6.1 (S), S6.2 (S1)
DOWN: IC1.9 (PD5/A5), S4.1 (S), S4.2 (S1)
GND: C1.2, C2.1, C3.1, IC1.14 (VSS), S1.3, S1.4 (P1), S2.3, S2.4 (P1), S3.3, S3.4 (P1), S4.3, S4.4 (P1), S5.3, S5.4 (P1), S6.3, S6.4 (P1), S7.3, S7.4 (P1), X1.5, X1.M1 (S1), X1.M2 (S2), X1.M3 (S3), X1.M4 (S4), X2.5, X2.6, X2.7, X2.8, X2.9, X2.10, X3.1, X4.2
HSYNC: IC1.8 (PD4/A7), X2.13
LEFT: IC1.1 (PC1), S1.1 (S), S1.2 (S1)
unnamed: R1.2, X2.1, X2.2, X2.3
unnamed: R4.1, X3.2, X3.3, X3.4, X3.5
RIGHT: IC1.2 (PC2), S3.1 (S), S3.2 (S1)
SWIO: IC1.7 (PD1/SWIO), X4.3
UP: IC1.10 (PD6/A6), S2.1 (S), S2.2 (S1)
VCC: C1.1, IC1.15 (VDD), X1.1, X4.1
VIDEO: IC1.5 (PC6), R1.1
VSYNC: IC1.6 (PC7), X2.14
X: IC1.11 (PD7/RST), S7.1 (S), S7.2 (S1)
XI: C2.2, IC1.12 (PA1/XI/A1), Q1.2
XO: C3.2, IC1.13 (PA2/XO/A0), Q1.1

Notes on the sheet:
5V/3.3V
GND
SWIO
Optional Crystal

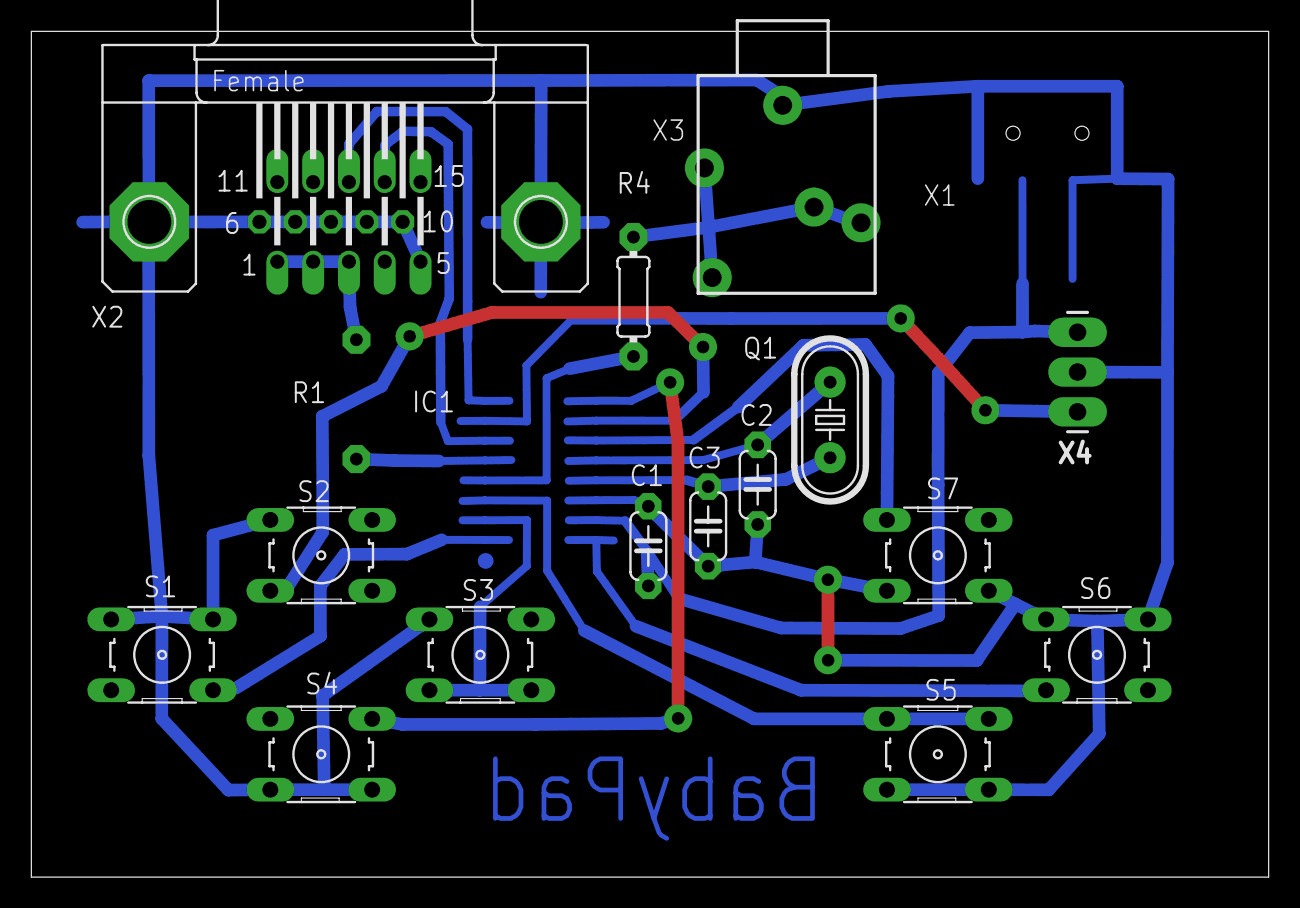
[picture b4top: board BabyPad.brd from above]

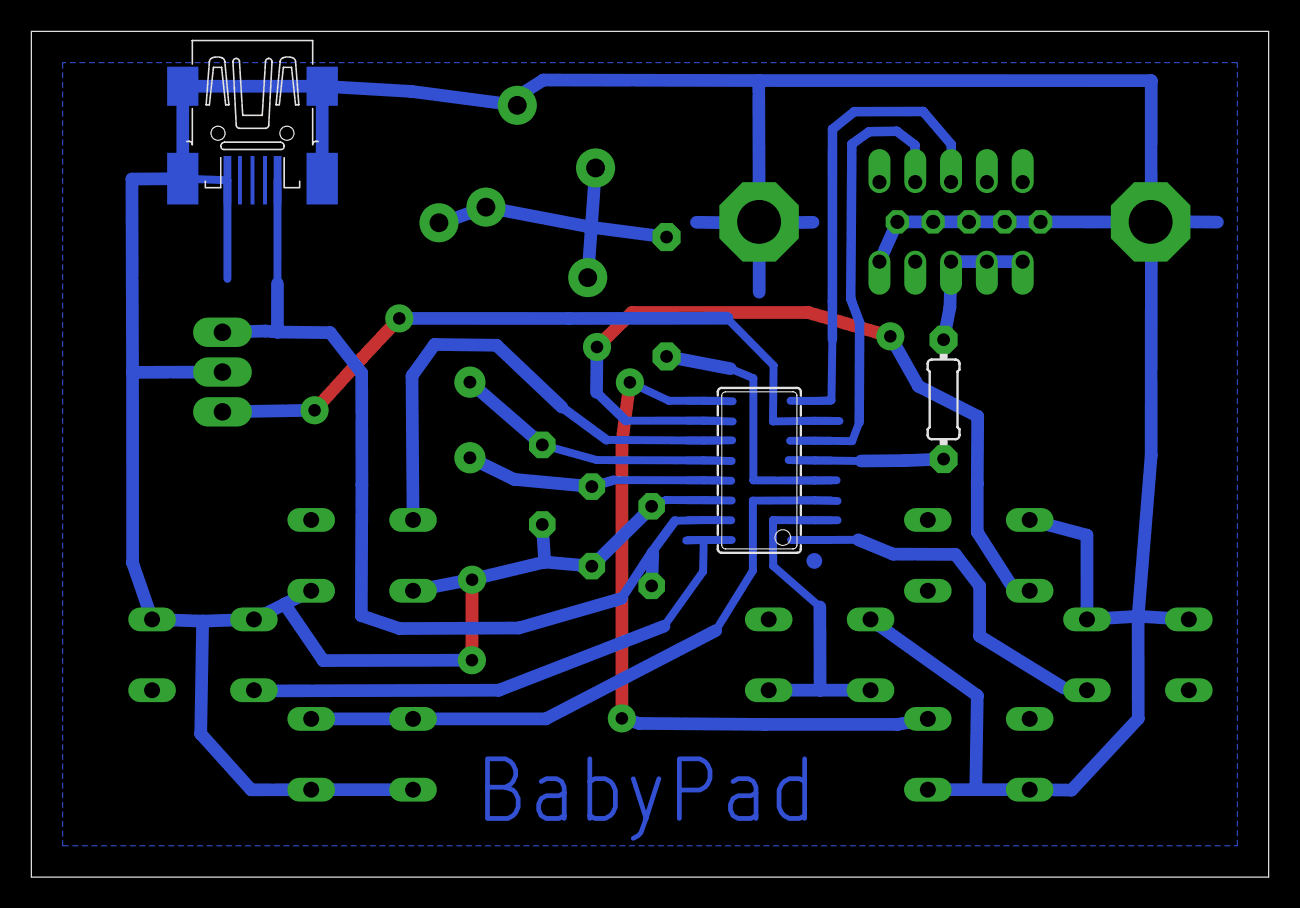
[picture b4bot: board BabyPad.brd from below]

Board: 2 copper layers, 79.0 x 54.0 mm, 18 parts (3 on the bottom side), 18 nets.

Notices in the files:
parts and their libraries:
SparkFun-Connectors: Licensing: Creative Commons ShareAlike 4.0 International - https://creativecommons.org/licenses/by-sa/4.0
Wuerth_Elektronik_eiCan_Communication_Co: Copyright: Würth Elektronik
